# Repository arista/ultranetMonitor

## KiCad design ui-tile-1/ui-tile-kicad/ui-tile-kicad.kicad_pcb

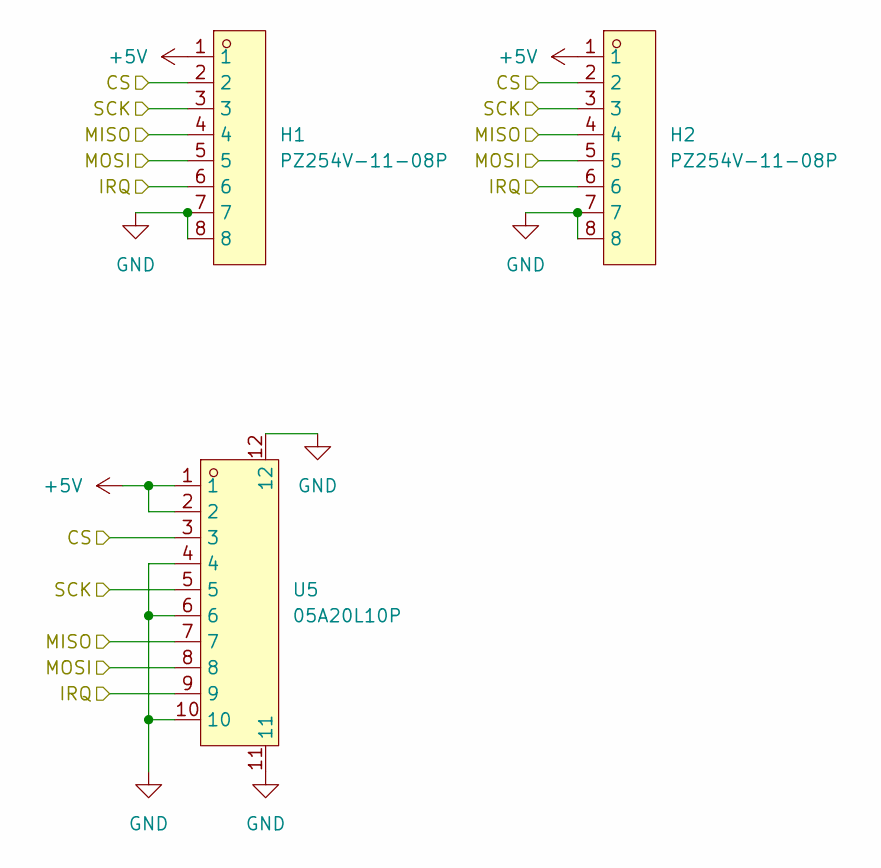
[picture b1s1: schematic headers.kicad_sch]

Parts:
H1, H2: PZ254V-11-08P; HDR-TH_8P-P2.54-V-M; MPN PZ254V-11-08P; LCSC Part C492407
U5: 05A20L10P; FPC-SMD_10P-P0.50_05A20L10P; MPN 05A20L10P; LCSC Part C5362154

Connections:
+5V: H1.1, H2.1, U5.1, U5.2; also elsewhere on the board
/headers/CS: H1.2, H2.2, U5.3; also elsewhere on the board
/headers/IRQ: H1.6, H2.6, U5.9; also elsewhere on the board
/headers/MISO: H1.4, H2.4, U5.7; also elsewhere on the board
/headers/MOSI: H1.5, H2.5, U5.8; also elsewhere on the board
/headers/SCK: H1.3, H2.3, U5.5; also elsewhere on the board
GND: H1.7, H1.8, H2.7, H2.8, U5.4, U5.6, U5.10, U5.11, U5.12; also elsewhere on the board

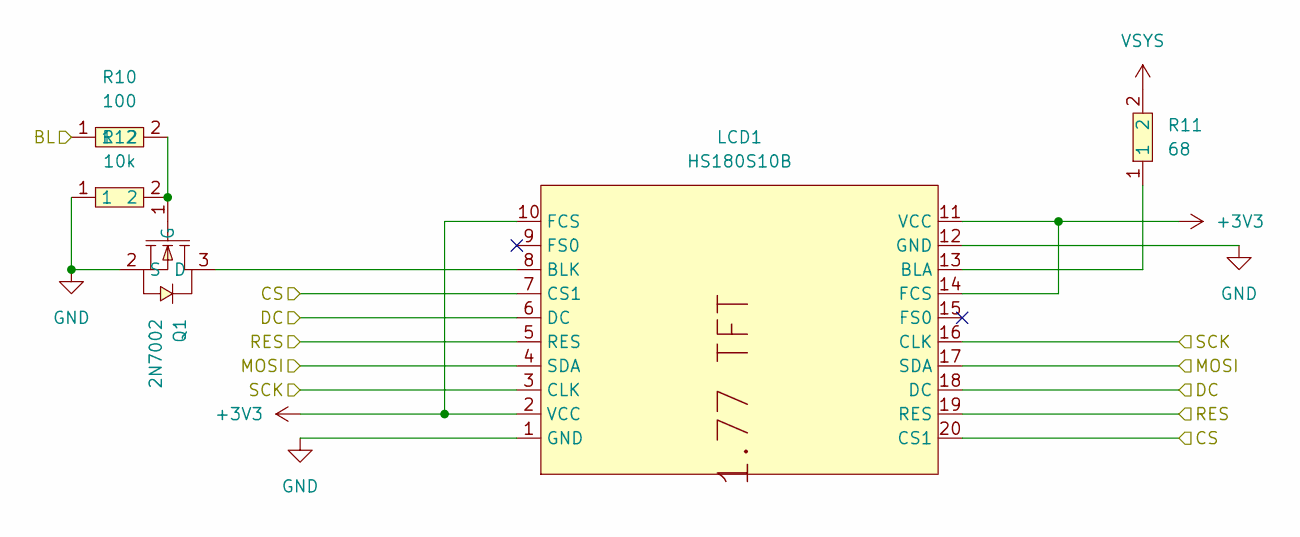
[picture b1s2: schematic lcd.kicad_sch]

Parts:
LCD1: HS180S10B; LCD-TH_L56.0-W35.0-P2.54_HS180S10B; MPN HS180S10B; LCSC Part C5329585
Q1: 2N7002; SOT-23-3_L2.9-W1.3-P1.90-LS2.4-BR; MPN 2N7002; LCSC Part C8545
R10: 100; R0402; MPN 0402WGF1000TCE; LCSC Part C25076
R11: 68; R0603; MPN 0603WAF680JT5E; LCSC Part C27592
R12: 10k; R0402; MPN 0402WGF1002TCE; LCSC Part C25744

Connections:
+3V3: LCD1.2 (VCC), LCD1.10 (FCS), LCD1.11 (VCC), LCD1.14 (FCS); also elsewhere on the board
/lcd/BL: R10.1; also elsewhere on the board
/lcd/CS: LCD1.7 (CS1), LCD1.20 (CS1); also elsewhere on the board
/lcd/DC: LCD1.6 (DC), LCD1.18 (DC); also elsewhere on the board
/lcd/MOSI: LCD1.4 (SDA), LCD1.17 (SDA); also elsewhere on the board
/lcd/RES: LCD1.5 (RES), LCD1.19 (RES); also elsewhere on the board
/lcd/SCK: LCD1.3 (CLK), LCD1.16 (CLK); also elsewhere on the board
GND: LCD1.1 (GND), LCD1.12 (GND), Q1.2 (S), R12.1; also elsewhere on the board
unnamed: LCD1.13 (BLA), R11.1
unnamed: LCD1.8 (BLK), Q1.3 (D)
unnamed: Q1.1 (G), R10.2, R12.2
VSYS: R11.2; also elsewhere on the board

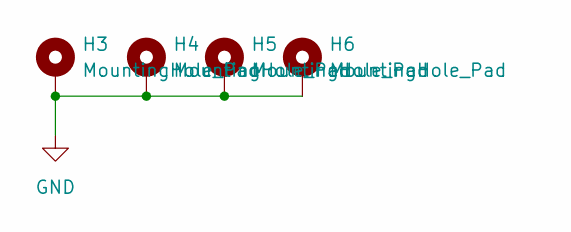
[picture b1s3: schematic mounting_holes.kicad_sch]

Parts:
H3, H4, H5, H6: MountingHole_Pad; MountingHole_3.2mm_M3_Pad

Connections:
GND: H3.1 (1_1), H4.1 (1_1), H5.1 (1_1), H6.1 (1_1); also elsewhere on the board

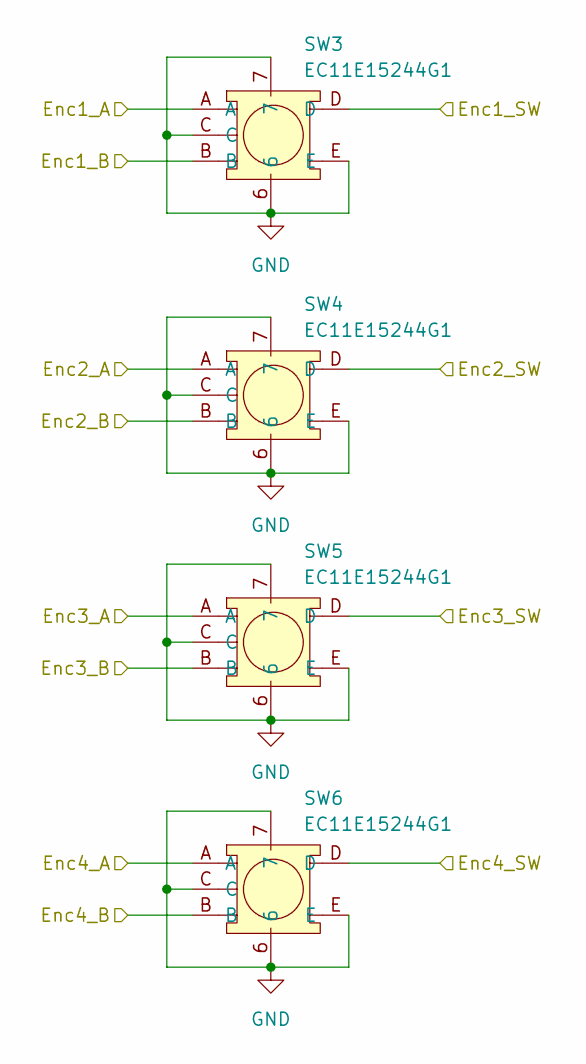
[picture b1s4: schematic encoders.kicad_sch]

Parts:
SW3, SW4, SW5, SW6: EC11E15244G1; SW-TH_EC11E15244G1; MPN EC11E15244G1; LCSC Part C370970

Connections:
/encoders/Enc1_A: SW3.A; also elsewhere on the board
/encoders/Enc1_B: SW3.B; also elsewhere on the board
/encoders/Enc1_SW: SW3.D; also elsewhere on the board
/encoders/Enc2_A: SW4.A; also elsewhere on the board
/encoders/Enc2_B: SW4.B; also elsewhere on the board
/encoders/Enc2_SW: SW4.D; also elsewhere on the board
/encoders/Enc3_A: SW5.A; also elsewhere on the board
/encoders/Enc3_B: SW5.B; also elsewhere on the board
/encoders/Enc3_SW: SW5.D; also elsewhere on the board
/encoders/Enc4_A: SW6.A; also elsewhere on the board
/encoders/Enc4_B: SW6.B; also elsewhere on the board
/encoders/Enc4_SW: SW6.D; also elsewhere on the board
GND: SW3.6, SW3.7, SW3.C, SW3.E, SW4.6, SW4.7, SW4.C, SW4.E, SW5.6, SW5.7, SW5.C, SW5.E, SW6.6, SW6.7, SW6.C, SW6.E; also elsewhere on the board

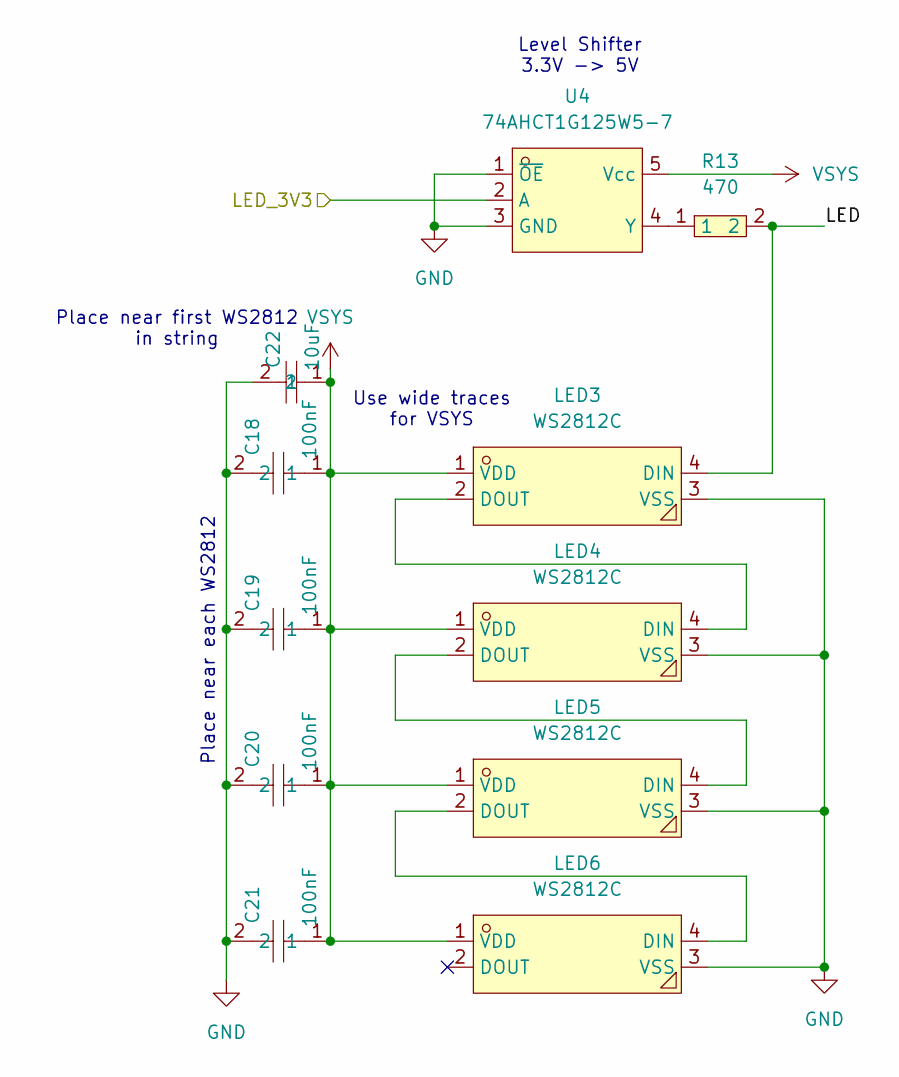
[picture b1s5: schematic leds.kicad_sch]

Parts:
C18, C19, C20, C21: 100nF; C0402; MPN CL05B104KO5NNNC; LCSC Part C1525
C22: 10uF; C0805; MPN CL21A106KOQNNNE; LCSC Part C1713
LED3, LED4, LED5, LED6: WS2812C; LED-SMD_4P-L5.0-W5.0-LS5.4-TL-1; MPN WS2812C; LCSC Part C114587
R13: 470; R0402; MPN 0402WGF4700TCE; LCSC Part C25117
U4: 74AHCT1G125W5-7; SOT-25-5_L3.0-W1.6-P0.95-LS2.8-BL; MPN 74AHCT1G125W5-7; LCSC Part C842287

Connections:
/leds/LED: LED3.4 (DIN), R13.2
/leds/LED_3V3: U4.2 (A); also elsewhere on the board
GND: C18.2, C19.2, C20.2, C21.2, C22.2, LED3.3 (VSS), LED4.3 (VSS), LED5.3 (VSS), LED6.3 (VSS), U4.1 (~OE), U4.3 (GND); also elsewhere on the board
unnamed: LED3.2 (DOUT), LED4.4 (DIN)
unnamed: LED4.2 (DOUT), LED5.4 (DIN)
unnamed: LED5.2 (DOUT), LED6.4 (DIN)
unnamed: R13.1, U4.4 (Y)
VSYS: C18.1, C19.1, C20.1, C21.1, C22.1, LED3.1 (VDD), LED4.1 (VDD), LED5.1 (VDD), LED6.1 (VDD), U4.5 (Vcc); also elsewhere on the board

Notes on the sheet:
Place near first WS2812 in string
Place near each WS2812
Use wide traces for VSYS
Level Shifter 3.3V -> 5V

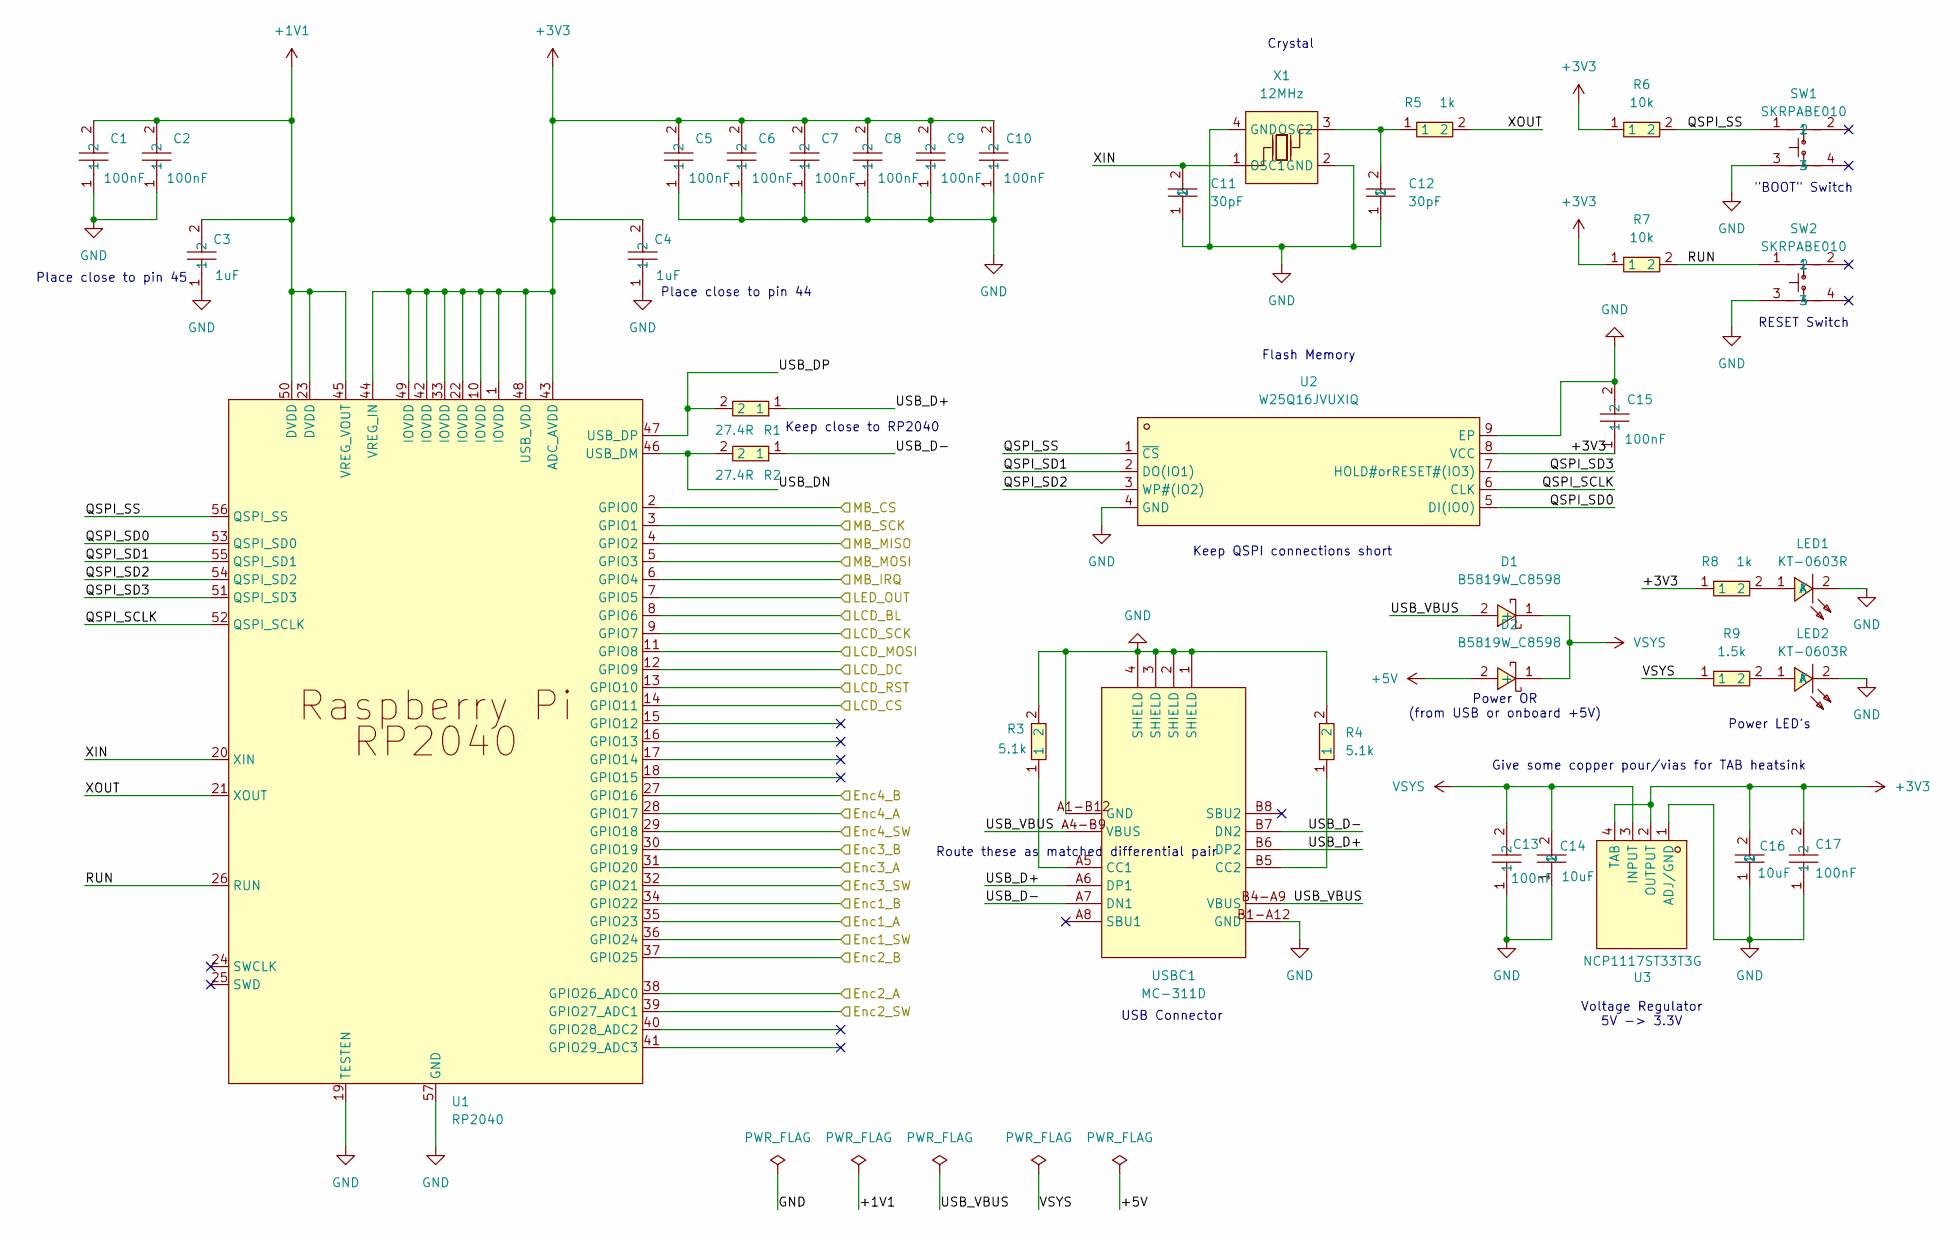
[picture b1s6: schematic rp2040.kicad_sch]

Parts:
C1, C2, C5, C6, C7, C8, C9, C10, C13, C15, C17: 100nF; C0402; MPN CL05B104KO5NNNC; LCSC Part C1525
C3, C4: 1uF; C0402; MPN CL05A105KA5NQNC; LCSC Part C52923
C11, C12: 30pF; C0402; MPN 0402CG300J500NT; LCSC Part C1570
C14, C16: 10uF; C0805; MPN CL21A106KOQNNNE; LCSC Part C1713
D1, D2: B5819W_C8598; SOD-123_L2.7-W1.6-LS3.7-RD-1; MPN B5819W SL; LCSC Part C8598
LED1, LED2: KT-0603R; LED-SMD_L1.6-W0.8-R-RD; MPN KT-0603R; LCSC Part C2286
R1, R2: 27.4R; R0402; MPN 0402WGF274JTCE; LCSC Part C31439
R3, R4: 5.1k; R0402; MPN 0402WGF5101TCE; LCSC Part C25905
R5, R8: 1k; R0402; MPN 0402WGF1001TCE; LCSC Part C11702
R6, R7: 10k; R0402; MPN 0402WGF1002TCE; LCSC Part C25744
R9: 1.5k; R0603; MPN 0603WAF1501T5E; LCSC Part C22843
SW1, SW2: SKRPABE010; KEY-SMD_4P-L4.2-W3.2-P2.20-LS4.6; MPN SKRPABE010; LCSC Part C115360
U1: RP2040; LQFN-56_L7.0-W7.0-P0.4-EP; MPN RP2040; LCSC Part C2040
U2: W25Q16JVUXIQ; USON-8_L3.0-W2.0-P0.50-BL-EP; MPN W25Q16JVUXIQ; LCSC Part C2843335
U3: NCP1117ST33T3G; SOT-223-3_L6.5-W3.4-P2.30-LS7.0-BR; MPN NCP1117ST33T3G; LCSC Part C26537
USBC1: MC-311D; USB-C-SMD_MC-311D; MPN MC-311D; LCSC Part C136423
X1: 12MHz; CRYSTAL-SMD_4P-L3.2-W2.5-BL; MPN X322512MSB4SI; LCSC Part C9002

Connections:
+1V1: C1.2, C2.2, C3.2, U1.23 (DVDD), U1.45 (VREG_VOUT), U1.50 (DVDD)
+3V3: C4.2, C5.2, C6.2, C7.2, C8.2, C9.2, C10.2, C15.1, C16.2, C17.2, R6.1, R7.1, R8.1, U1.1 (IOVDD), U1.10 (IOVDD), U1.22 (IOVDD), U1.33 (IOVDD), U1.42 (IOVDD), U1.43 (ADC_AVDD), U1.44 (VREG_IN), U1.48 (USB_VDD), U1.49 (IOVDD), U2.8 (VCC), U3.2 (OUTPUT), U3.4 (TAB); also elsewhere on the board
+5V: D2.2 (+); also elsewhere on the board
/encoders/Enc1_A: U1.35 (GPIO23); also elsewhere on the board
/encoders/Enc1_B: U1.34 (GPIO22); also elsewhere on the board
/encoders/Enc1_SW: U1.36 (GPIO24); also elsewhere on the board
/encoders/Enc2_A: U1.38 (GPIO26_ADC0); also elsewhere on the board
/encoders/Enc2_B: U1.37 (GPIO25); also elsewhere on the board
/encoders/Enc2_SW: U1.39 (GPIO27_ADC1); also elsewhere on the board
/encoders/Enc3_A: U1.31 (GPIO20); also elsewhere on the board
/encoders/Enc3_B: U1.30 (GPIO19); also elsewhere on the board
/encoders/Enc3_SW: U1.32 (GPIO21); also elsewhere on the board
/encoders/Enc4_A: U1.28 (GPIO17); also elsewhere on the board
/encoders/Enc4_B: U1.27 (GPIO16); also elsewhere on the board
/encoders/Enc4_SW: U1.29 (GPIO18); also elsewhere on the board
/headers/CS: U1.2 (GPIO0); also elsewhere on the board
/headers/IRQ: U1.6 (GPIO4); also elsewhere on the board
/headers/MISO: U1.4 (GPIO2); also elsewhere on the board
/headers/MOSI: U1.5 (GPIO3); also elsewhere on the board
/headers/SCK: U1.3 (GPIO1); also elsewhere on the board
/lcd/BL: U1.8 (GPIO6); also elsewhere on the board
/lcd/CS: U1.14 (GPIO11); also elsewhere on the board
/lcd/DC: U1.12 (GPIO9); also elsewhere on the board
/lcd/MOSI: U1.11 (GPIO8); also elsewhere on the board
/lcd/RES: U1.13 (GPIO10); also elsewhere on the board
/lcd/SCK: U1.9 (GPIO7); also elsewhere on the board
/leds/LED_3V3: U1.7 (GPIO5); also elsewhere on the board
/rp2040/QSPI_SCLK: U1.52 (QSPI_SCLK), U2.6 (CLK)
/rp2040/QSPI_SD0: U1.53 (QSPI_SD0), U2.5 (DI(IO0))
/rp2040/QSPI_SD1: U1.55 (QSPI_SD1), U2.2 (DO(IO1))
/rp2040/QSPI_SD2: U1.54 (QSPI_SD2), U2.3 (WP#(IO2))
/rp2040/QSPI_SD3: U1.51 (QSPI_SD3), U2.7 (HOLD#orRESET#(IO3))
/rp2040/QSPI_SS: R6.2, SW1.1, U1.56 (QSPI_SS), U2.1 (~CS)
/rp2040/RUN: R7.2, SW2.1, U1.26 (RUN)
/rp2040/USB_D+: R1.1, USBC1.A6 (DP1), USBC1.B6 (DP2)
/rp2040/USB_D-: R2.1, USBC1.A7 (DN1), USBC1.B7 (DN2)
/rp2040/USB_DN: R2.2, U1.46 (USB_DM)
/rp2040/USB_DP: R1.2, U1.47 (USB_DP)
/rp2040/USB_VBUS: D1.2 (+), USBC1.A4-B9 (VBUS), USBC1.B4-A9 (VBUS)
/rp2040/XIN: C11.2, U1.20 (XIN), X1.1 (OSC1)
/rp2040/XOUT: R5.2, U1.21 (XOUT)
GND: C1.1, C2.1, C3.1, C4.1, C5.1, C6.1, C7.1, C8.1, C9.1, C10.1, C11.1, C12.1, C13.1, C14.1, C15.2, C16.1, C17.1, LED1.2 (K), LED2.2 (K), R3.2, R4.2, SW1.3, SW2.3, U1.19 (TESTEN), U1.57 (GND), U2.4 (GND), U2.9 (EP), U3.1 (ADJ/GND), USBC1.1 (SHIELD), USBC1.2 (SHIELD), USBC1.3 (SHIELD), USBC1.4 (SHIELD), USBC1.A1-B12 (GND), USBC1.B1-A12 (GND), X1.2 (GND), X1.4 (GND); also elsewhere on the board
unnamed: LED1.1 (A), R8.2
unnamed: LED2.1 (A), R9.2
unnamed: R3.1, USBC1.A5 (CC1)
unnamed: R4.1, USBC1.B5 (CC2)
unnamed: C12.2, R5.1, X1.3 (OSC2)
VSYS: C13.2, C14.2, D1.1 (-), D2.1 (-), R9.1, U3.3 (INPUT); also elsewhere on the board

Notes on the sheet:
Route these as matched differential pair
Give some copper pour/vias for TAB heatsink
Crystal
RESET Switch
"BOOT" Switch
Flash Memory
Place close to pin 45
Voltage Regulator 5V -> 3.3V
Keep QSPI connections short
Keep close to RP2040
Power LED's
Power OR (from USB or onboard +5V)
USB Connector
Place close to pin 44

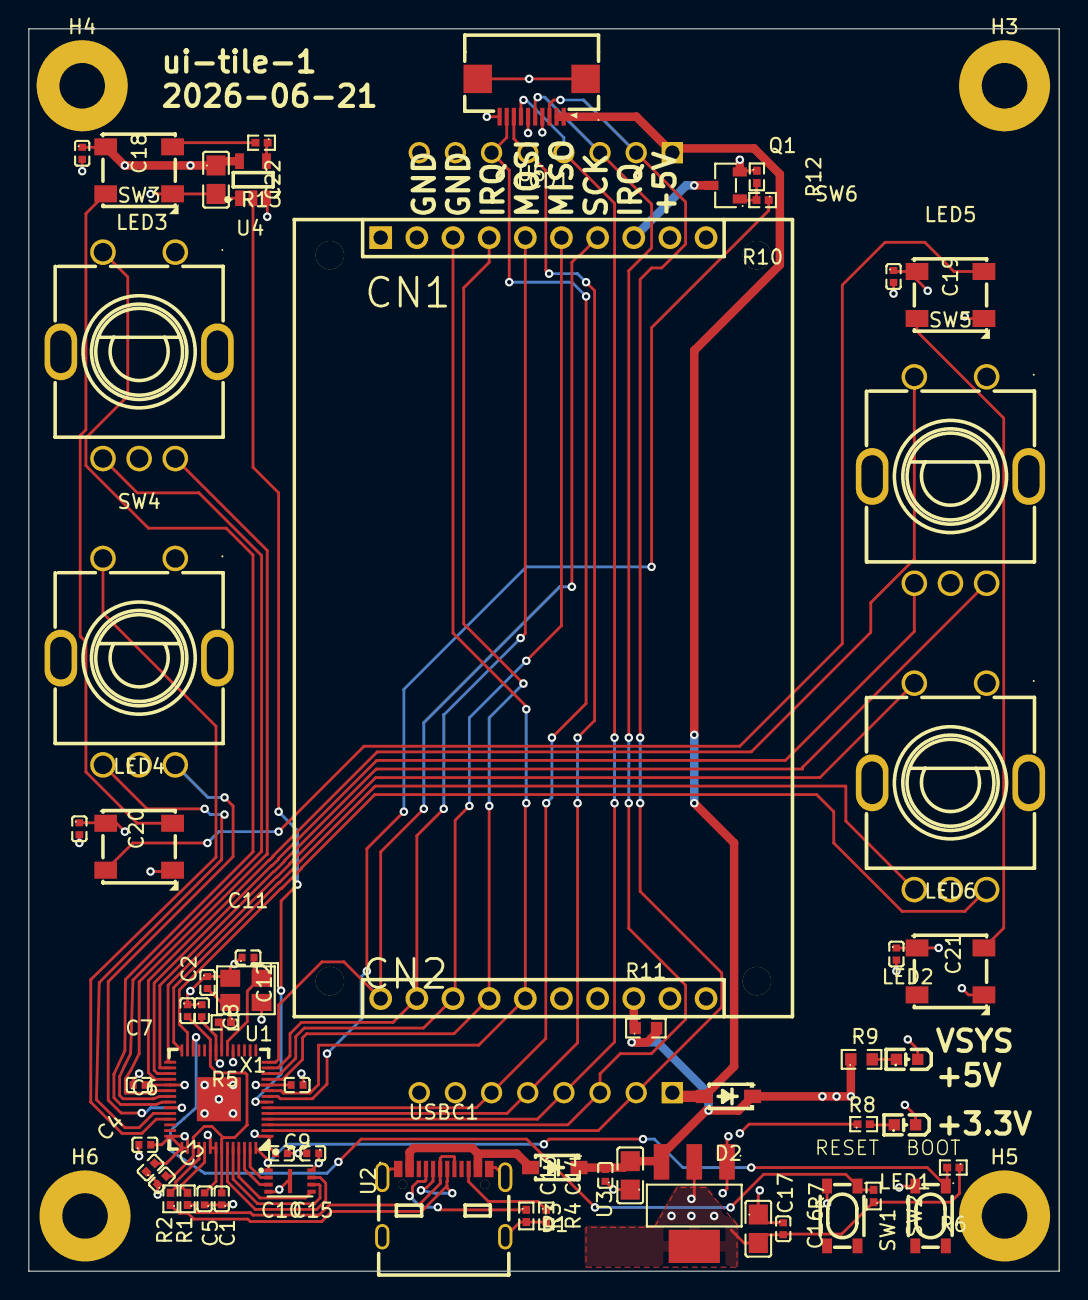
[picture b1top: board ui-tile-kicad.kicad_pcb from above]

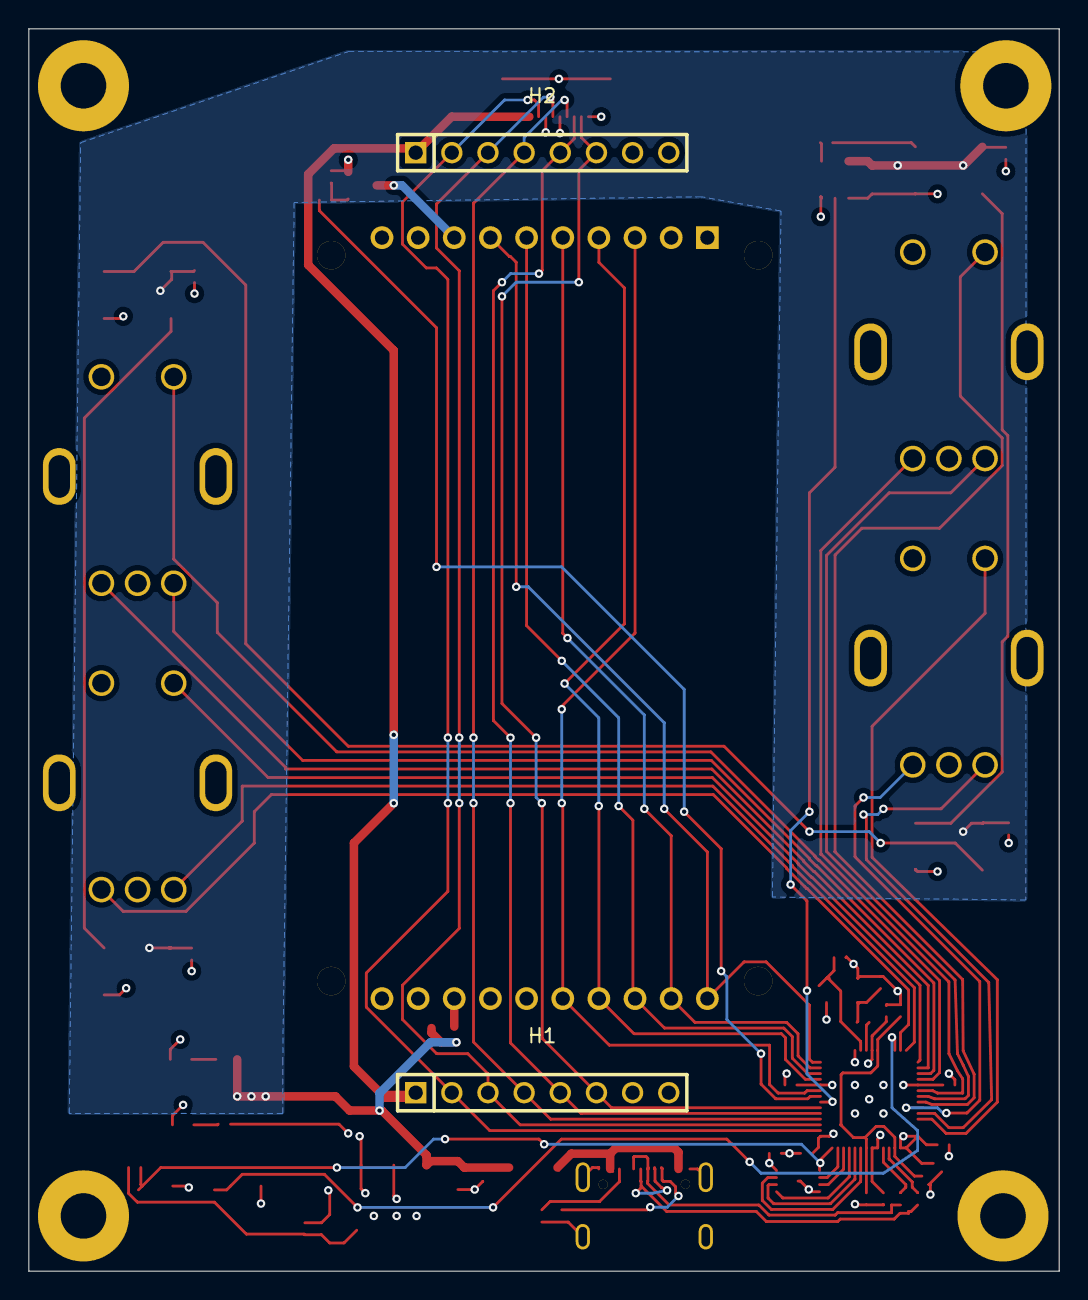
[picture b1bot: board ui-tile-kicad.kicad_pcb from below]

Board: 4 copper layers, 72.4 x 87.3 mm, 64 parts (2 on the bottom side), 56 nets.

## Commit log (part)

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2026-06-16 removed install-kicad
2026-06-19 started on ui tile schematic
2026-06-19 continuing with ui-tile
2026-06-19 removed warnings from schematic
2026-06-19 finished first pass at rp2040 basics
2026-06-19 started breaking out into sub sheets
2026-06-19 started on ws2812's
2026-06-19 added next steps to PLANS.md
2026-06-20 finished schematic electricals
2026-06-20 preparing for pcb layout
2026-06-20 brought in erc fixes
2026-06-20 progress on pcb layout
2026-06-21 finished first pass of pcb layout
2026-06-21 moved regulator away from board edge
2026-06-21 Added mounting holes
2026-06-21 added fpc connector
2026-06-21 added some labeling
2026-06-21 marked the two headers as exclude from position files and exclude from bill of materials
2026-06-21 snapshot of the board ordered from jlcpcb - ui-tile-1 2026-06-21
